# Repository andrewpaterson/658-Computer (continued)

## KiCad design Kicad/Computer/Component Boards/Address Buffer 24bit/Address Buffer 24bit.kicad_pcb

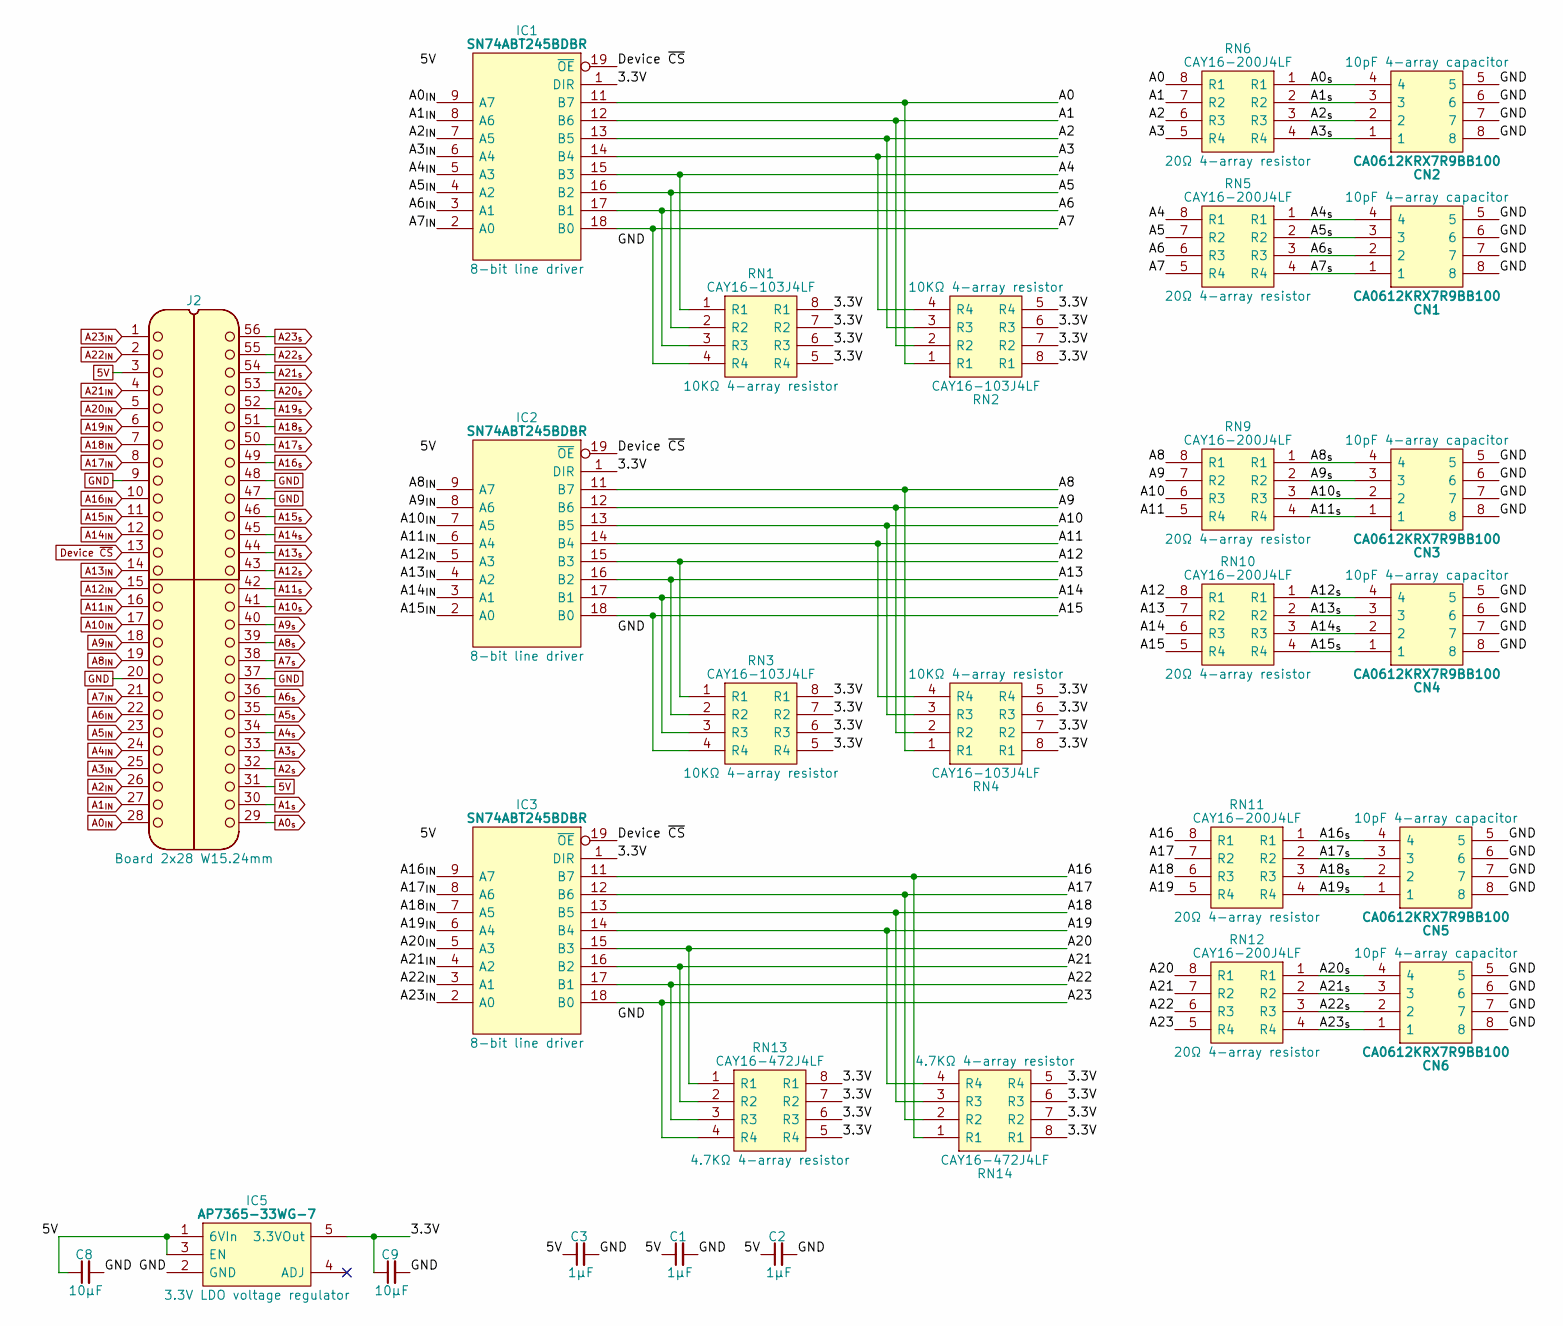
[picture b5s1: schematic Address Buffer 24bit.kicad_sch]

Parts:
C1, C2, C3: 1μF; C_0805
C8, C9: 10µF; C_0805
CN1, CN2, CN3, CN4, CN5, CN6: CA0612KRX7R9BB100; Manufacturer_Part_Number CA0612KRX7R9BB102; Mouser Part Number 603-CA612KRX7R9BB102
IC1, IC2, IC3: SN74ABT245BDBR; SOP65P780X200-20N; Manufacturer_Part_Number SN74ABT245BDBR; Mouser Part Number 595-SN74ABT245BDBR
IC5: AP7365-33WG-7; SOT95P285X130-5N; Manufacturer_Part_Number AP7365-33WG-7; Mouser Part Number 621-AP7365-33WG-7
J2: Board 2x28 W15.24mm; DIP-56_Board_W15.24mm
RN1, RN2, RN3, RN4: CAY16-103J4LF; CAY16-J4; Manufacturer_Part_Number CAY16-103J4LF; Mouser Part Number 652-CAY16-103J4LF
RN5, RN6, RN9, RN10, RN11, RN12: CAY16-200J4LF; CAY16-F4; Manufacturer_Part_Number CAY16-331J4LF; Mouser Part Number 652-CAY16-331J4LF
RN13, RN14: CAY16-472J4LF; CAY16-F4; Manufacturer_Part_Number CAY16-472J4LF; Mouser Part Number 652-CAY16-472J4LF

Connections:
5V: C1.1, C2.1, C3.1, C8.1, IC1.20 (5V), IC2.20 (5V), IC3.20 (5V), IC5.1 (6VIn), IC5.3 (EN), J2.3, J2.31
/3.3V: C9.1, IC1.1 (DIR), IC2.1 (DIR), IC3.1 (DIR), IC5.5 (3.3VOut), RN1.5 (R4), RN1.6 (R3), RN1.7 (R2), RN1.8 (R1), RN2.5 (R4), RN2.6 (R3), RN2.7 (R2), RN2.8 (R1), RN3.5 (R4), RN3.6 (R3), RN3.7 (R2), RN3.8 (R1), RN4.5 (R4), RN4.6 (R3), RN4.7 (R2), RN4.8 (R1), RN13.5 (R4), RN13.6 (R3), RN13.7 (R2), RN13.8 (R1), RN14.5 (R4), RN14.6 (R3), RN14.7 (R2), RN14.8 (R1)
/A0: IC1.11 (B7), RN2.1 (R1), RN6.8 (R1)
/A1: IC1.12 (B6), RN2.2 (R2), RN6.7 (R2)
/A2: IC1.13 (B5), RN2.3 (R3), RN6.6 (R3)
/A3: IC1.14 (B4), RN2.4 (R4), RN6.5 (R4)
/A4: IC1.15 (B3), RN1.1 (R1), RN5.8 (R1)
/A5: IC1.16 (B2), RN1.2 (R2), RN5.7 (R2)
/A6: IC1.17 (B1), RN1.3 (R3), RN5.6 (R3)
/A7: IC1.18 (B0), RN1.4 (R4), RN5.5 (R4)
/A8: IC2.11 (B7), RN4.1 (R1), RN9.8 (R1)
/A9: IC2.12 (B6), RN4.2 (R2), RN9.7 (R2)
/A10: IC2.13 (B5), RN4.3 (R3), RN9.6 (R3)
/A11: IC2.14 (B4), RN4.4 (R4), RN9.5 (R4)
/A12: IC2.15 (B3), RN3.1 (R1), RN10.8 (R1)
/A13: IC2.16 (B2), RN3.2 (R2), RN10.7 (R2)
/A14: IC2.17 (B1), RN3.3 (R3), RN10.6 (R3)
/A15: IC2.18 (B0), RN3.4 (R4), RN10.5 (R4)
/A16: IC3.11 (B7), RN11.8 (R1), RN14.1 (R1)
/A17: IC3.12 (B6), RN11.7 (R2), RN14.2 (R2)
/A18: IC3.13 (B5), RN11.6 (R3), RN14.3 (R3)
/A19: IC3.14 (B4), RN11.5 (R4), RN14.4 (R4)
/A20: IC3.15 (B3), RN12.8 (R1), RN13.1 (R1)
/A21: IC3.16 (B2), RN12.7 (R2), RN13.2 (R2)
/A22: IC3.17 (B1), RN12.6 (R3), RN13.3 (R3)
/A23: IC3.18 (B0), RN12.5 (R4), RN13.4 (R4)
A0_{IN}: IC1.9 (A7), J2.28
A0_{s}: CN2.4, J2.29, RN6.1 (R1)
A1_{IN}: IC1.8 (A6), J2.27
A1_{s}: CN2.3, J2.30, RN6.2 (R2)
A2_{IN}: IC1.7 (A5), J2.26
A2_{s}: CN2.2, J2.32, RN6.3 (R3)
A3_{IN}: IC1.6 (A4), J2.25
A3_{s}: CN2.1, J2.33, RN6.4 (R4)
A4_{IN}: IC1.5 (A3), J2.24
A4_{s}: CN1.4, J2.34, RN5.1 (R1)
A5_{IN}: IC1.4 (A2), J2.23
A5_{s}: CN1.3, J2.35, RN5.2 (R2)
A6_{IN}: IC1.3 (A1), J2.22
A6_{s}: CN1.2, J2.36, RN5.3 (R3)
A7_{IN}: IC1.2 (A0), J2.21
A7_{s}: CN1.1, J2.38, RN5.4 (R4)
A8_{IN}: IC2.9 (A7), J2.19
A8_{s}: CN3.4, J2.39, RN9.1 (R1)
A9_{IN}: IC2.8 (A6), J2.18
A9_{s}: CN3.3, J2.40, RN9.2 (R2)
A10_{IN}: IC2.7 (A5), J2.17
A10_{s}: CN3.2, J2.41, RN9.3 (R3)
A11_{IN}: IC2.6 (A4), J2.16
A11_{s}: CN3.1, J2.42, RN9.4 (R4)
A12_{IN}: IC2.5 (A3), J2.15
A12_{s}: CN4.4, J2.43, RN10.1 (R1)
A13_{IN}: IC2.4 (A2), J2.14
A13_{s}: CN4.3, J2.44, RN10.2 (R2)
A14_{IN}: IC2.3 (A1), J2.12
A14_{s}: CN4.2, J2.45, RN10.3 (R3)
A15_{IN}: IC2.2 (A0), J2.11
A15_{s}: CN4.1, J2.46, RN10.4 (R4)
A16_{IN}: IC3.9 (A7), J2.10
A16_{s}: CN5.4, J2.49, RN11.1 (R1)
A17_{IN}: IC3.8 (A6), J2.8
A17_{s}: CN5.3, J2.50, RN11.2 (R2)
A18_{IN}: IC3.7 (A5), J2.7
A18_{s}: CN5.2, J2.51, RN11.3 (R3)
A19_{IN}: IC3.6 (A4), J2.6
A19_{s}: CN5.1, J2.52, RN11.4 (R4)
A20_{IN}: IC3.5 (A3), J2.5
A20_{s}: CN6.4, J2.53, RN12.1 (R1)
A21_{IN}: IC3.4 (A2), J2.4
A21_{s}: CN6.3, J2.54, RN12.2 (R2)
A22_{IN}: IC3.3 (A1), J2.2
A22_{s}: CN6.2, J2.55, RN12.3 (R3)
A23_{IN}: IC3.2 (A0), J2.1
A23_{s}: CN6.1, J2.56, RN12.4 (R4)
Device ~CS: IC1.19 (~OE), IC2.19 (~OE), IC3.19 (~OE), J2.13
GND: C1.2, C2.2, C3.2, C8.2, C9.2, CN1.5, CN1.6, CN1.7, CN1.8, CN2.5, CN2.6, CN2.7, CN2.8, CN3.5, CN3.6, CN3.7, CN3.8, CN4.5, CN4.6, CN4.7, CN4.8, CN5.5, CN5.6, CN5.7, CN5.8, CN6.5, CN6.6, CN6.7, CN6.8, IC1.10 (GND), IC2.10 (GND), IC3.10 (GND), IC5.2 (GND), J2.9, J2.20, J2.37, J2.47, J2.48

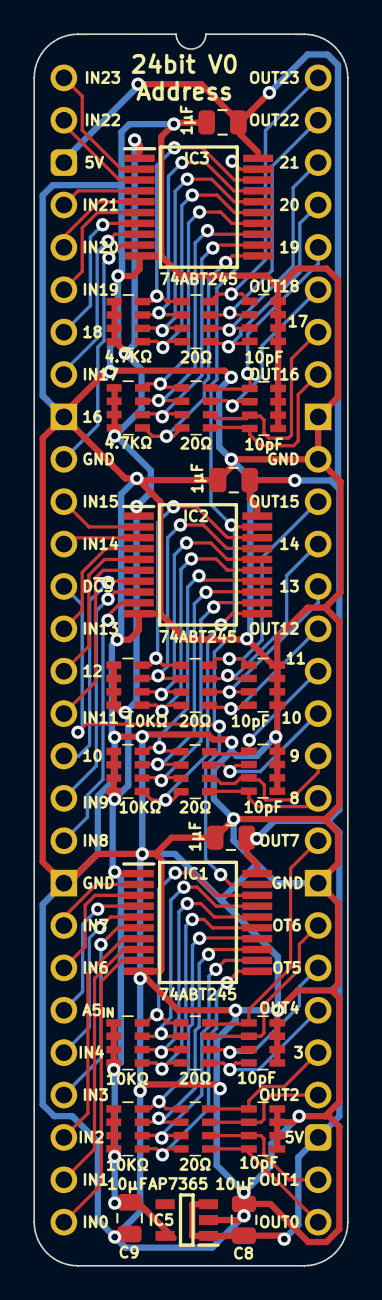
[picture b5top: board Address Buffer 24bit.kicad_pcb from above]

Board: 2 copper layers, 18.8 x 73.8 mm, 28 parts (0 on the bottom side), 76 nets.

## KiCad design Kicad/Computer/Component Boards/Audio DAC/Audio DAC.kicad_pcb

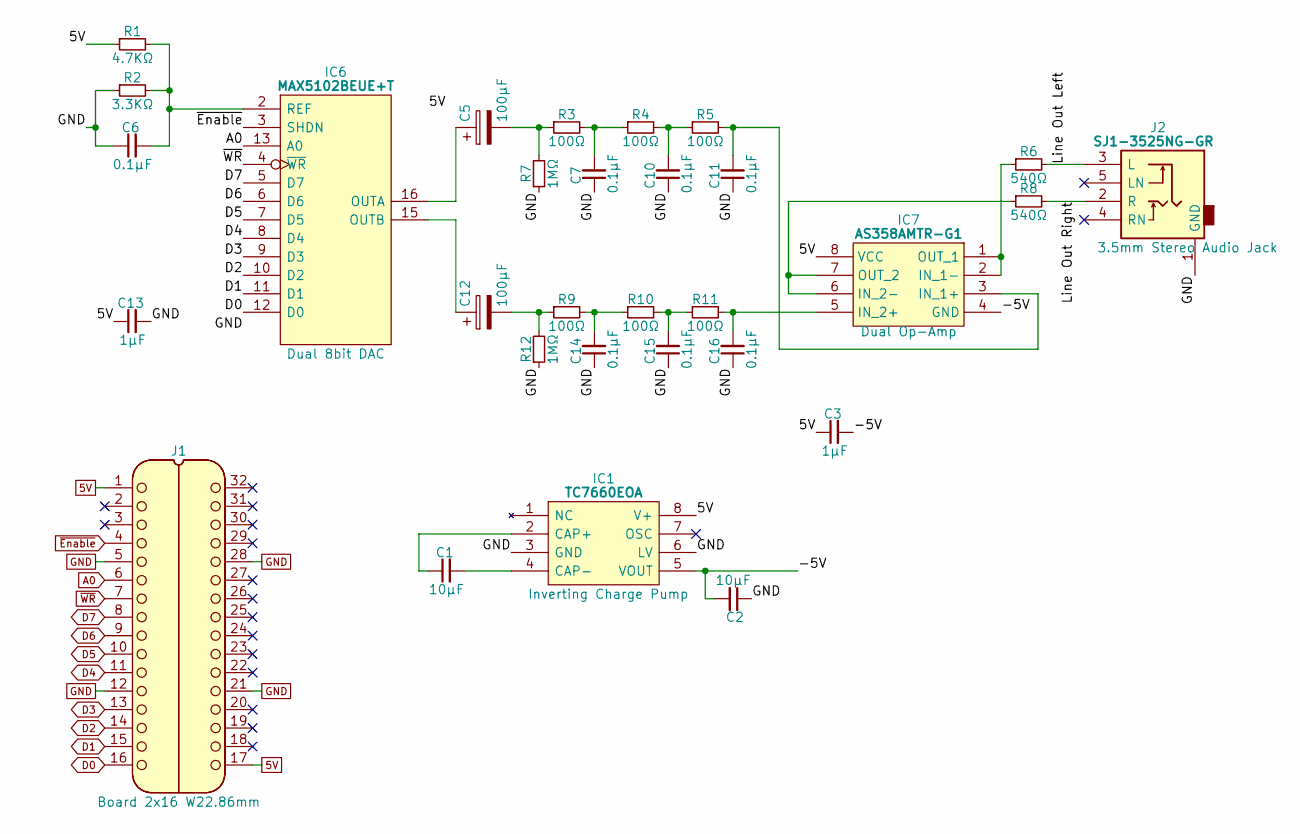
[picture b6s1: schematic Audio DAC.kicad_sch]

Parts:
C1, C2: 10µF; C_0805
C3, C13: 1μF; C_0805
C5, C12: 100μF; CP_Radial_D4.0mm_P2.00mm
C6, C7, C10, C11, C14, C15, C16: 0.1μF; C_0805
IC1: TC7660EOA; SOIC127P600X175-8N; Manufacturer_Part_Number TC7660EOA; Mouser Part Number 579-TC7660EOA
IC6: MAX5102BEUE+T; SOP65P640X110-16N; Manufacturer_Part_Number MAX5102BEUE+T; Mouser Part Number 700-MAX5102BEUET
IC7: AS358AMTR-G1; SOIC127P600X175-8N; Manufacturer_Part_Number AS358AMTR-G1
J1: Board 2x16 W22.86mm; DIP-32_Board_W22.86mm
J2: SJ1-3525NG-GR; SJ13525NGGR; Manufacturer_Part_Number SJ1-3525NG-GR; Mouser Part Number 490-SJ1-3525NG-GR
R1: 4.7KΩ; R_0805
R2: 3.3KΩ; R_0805
R3, R4, R5, R9, R10, R11: 100Ω; R_0805
R6, R8: 540Ω; R_0805
R7, R12: 1MΩ; R_0805

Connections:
5V: C3.1, C13.1, IC1.8 (V+), IC6.1 (VDD), IC7.8 (VCC), J1.1, J1.17, R1.1
/-5V: C2.2, C3.2, IC1.5 (VOUT), IC7.4 (GND)
/Line Out Left: J2.3 (L), R6.2
/Line Out Right: J2.2 (R), R8.2
A0: IC6.13 (A0), J1.6
D0: IC6.12 (D0), J1.16
D1: IC6.11 (D1), J1.15
D2: IC6.10 (D2), J1.14
D3: IC6.9 (D3), J1.13
D4: IC6.8 (D4), J1.11
D5: IC6.7 (D5), J1.10
D6: IC6.6 (D6), J1.9
D7: IC6.5 (D7), J1.8
GND: C2.1, C6.1, C7.1, C10.1, C11.1, C13.2, C14.1, C15.1, C16.1, IC1.3 (GND), IC1.6 (LV), IC6.14 (GND), J1.5, J1.12, J1.21, J1.28, J2.1 (GND), R2.1, R7.1, R12.1
unnamed: C5.2, R3.1, R7.2
unnamed: C7.2, R3.2, R4.1
unnamed: C10.2, R4.2, R5.1
unnamed: C12.2, R9.1, R12.2
unnamed: C14.2, R9.2, R10.1
unnamed: C15.2, R10.2, R11.1
unnamed: C1.1, IC1.2 (CAP+)
unnamed: C1.2, IC1.4 (CAP-)
unnamed: C5.1, IC6.16 (OUTA)
unnamed: C12.1, IC6.15 (OUTB)
unnamed: C6.2, IC6.2 (REF), R1.2, R2.2
unnamed: C11.2, IC7.3 (IN_1+), R5.2
unnamed: IC7.1 (OUT_1), IC7.2 (IN_1-), R6.1
unnamed: C16.2, IC7.5 (IN_2+), R11.2
unnamed: IC7.6 (IN_2-), IC7.7 (OUT_2), R8.1
~Enable: IC6.3 (SHDN), J1.4
~WR: IC6.4 (~WR), J1.7

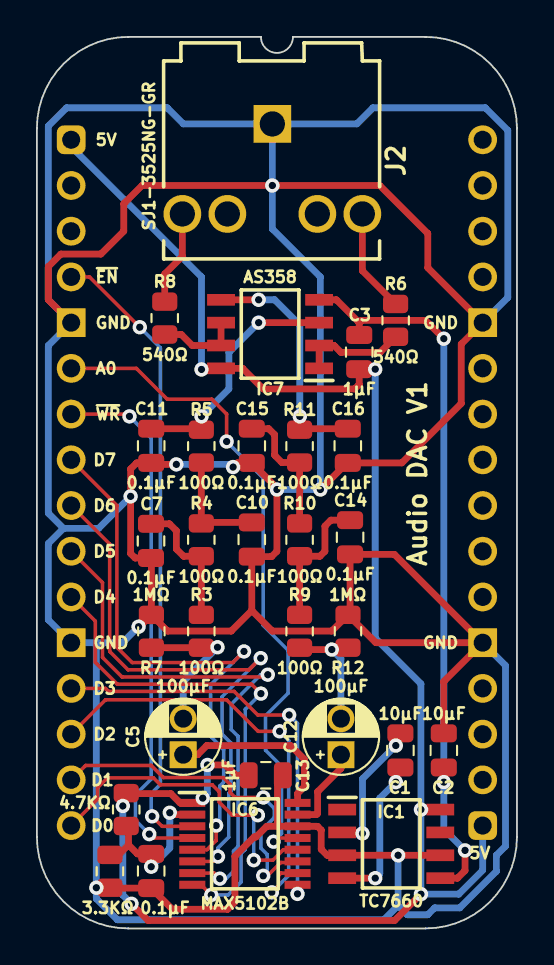
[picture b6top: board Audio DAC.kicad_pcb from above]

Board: 2 copper layers, 26.7 x 49.5 mm, 30 parts (0 on the bottom side), 31 nets.

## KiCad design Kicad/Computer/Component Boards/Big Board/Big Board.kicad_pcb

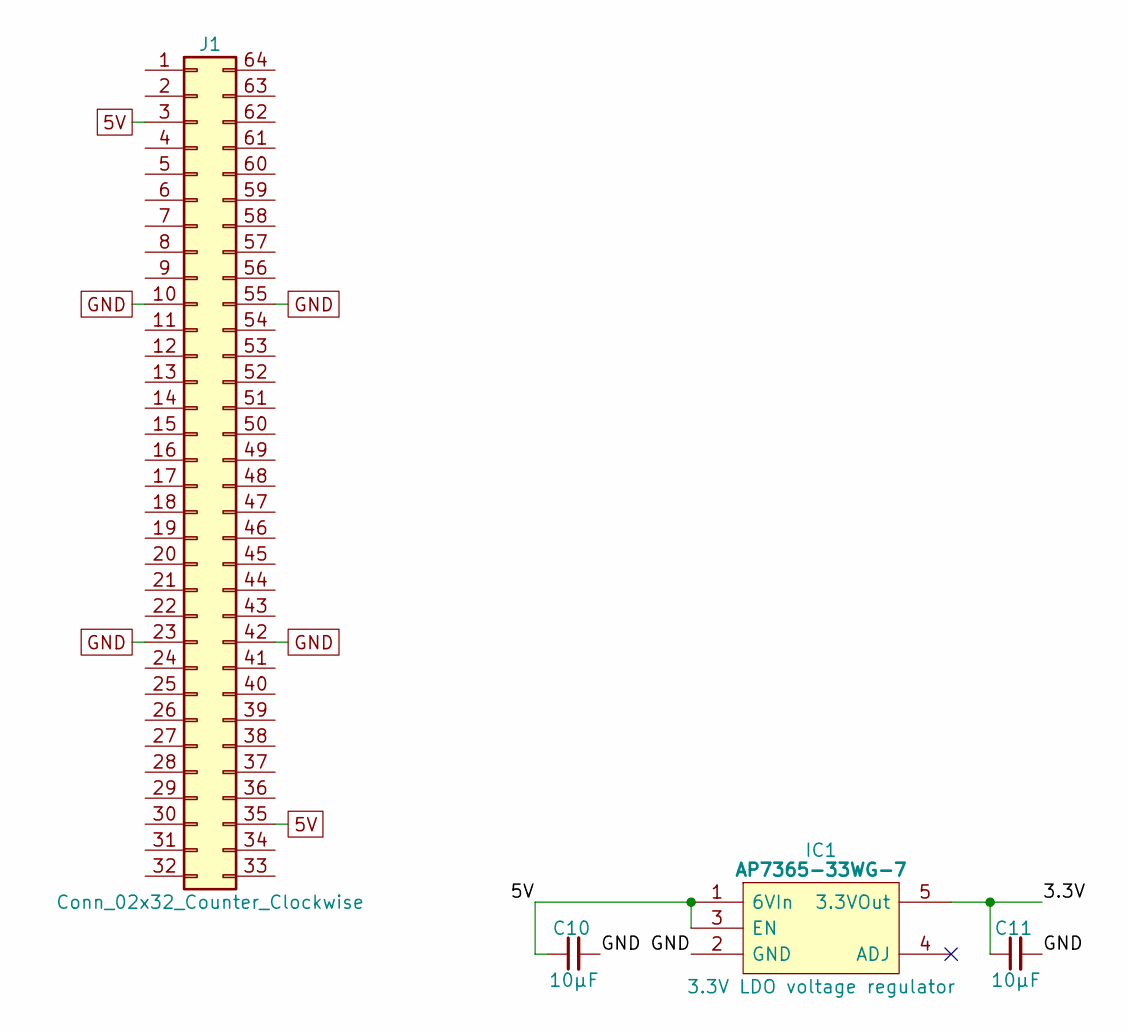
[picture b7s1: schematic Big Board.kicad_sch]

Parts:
C10, C11: 10µF; C_0805
IC1: AP7365-33WG-7; SOT95P285X130-5N; Manufacturer_Part_Number AP7365-33WG-7; Mouser Part Number 621-AP7365-33WG-7
J1: Conn_02x32_Counter_Clockwise; DIP-64_Board_W22.86mm

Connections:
5V: C10.1, IC1.1 (6VIn), IC1.3 (EN), J1.3, J1.35
/3.3V: C11.1, IC1.5 (3.3VOut)
GND: C10.2, C11.2, IC1.2 (GND), J1.10, J1.23, J1.42, J1.55

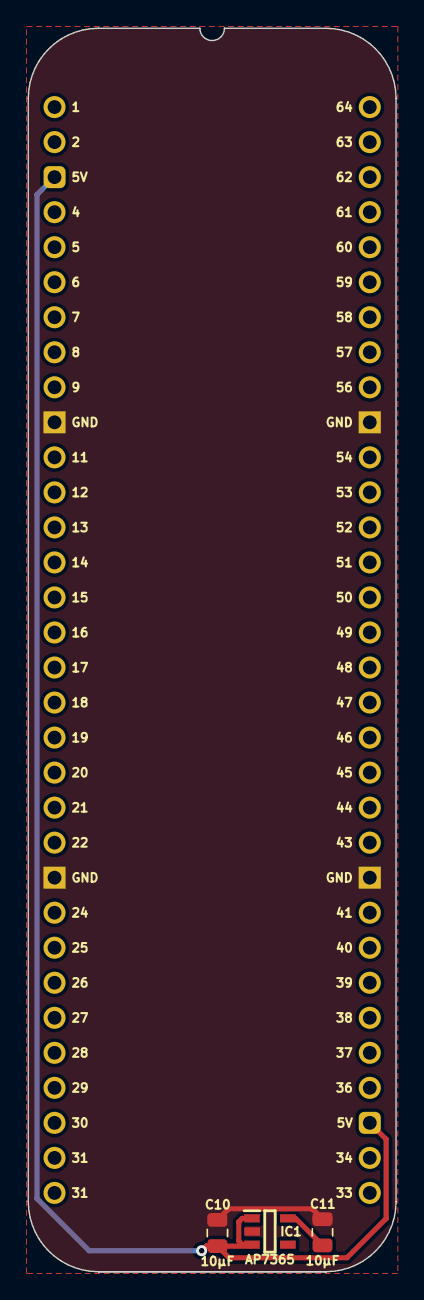
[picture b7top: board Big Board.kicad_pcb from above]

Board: 2 copper layers, 26.7 x 90.2 mm, 4 parts (0 on the bottom side), 3 nets.
